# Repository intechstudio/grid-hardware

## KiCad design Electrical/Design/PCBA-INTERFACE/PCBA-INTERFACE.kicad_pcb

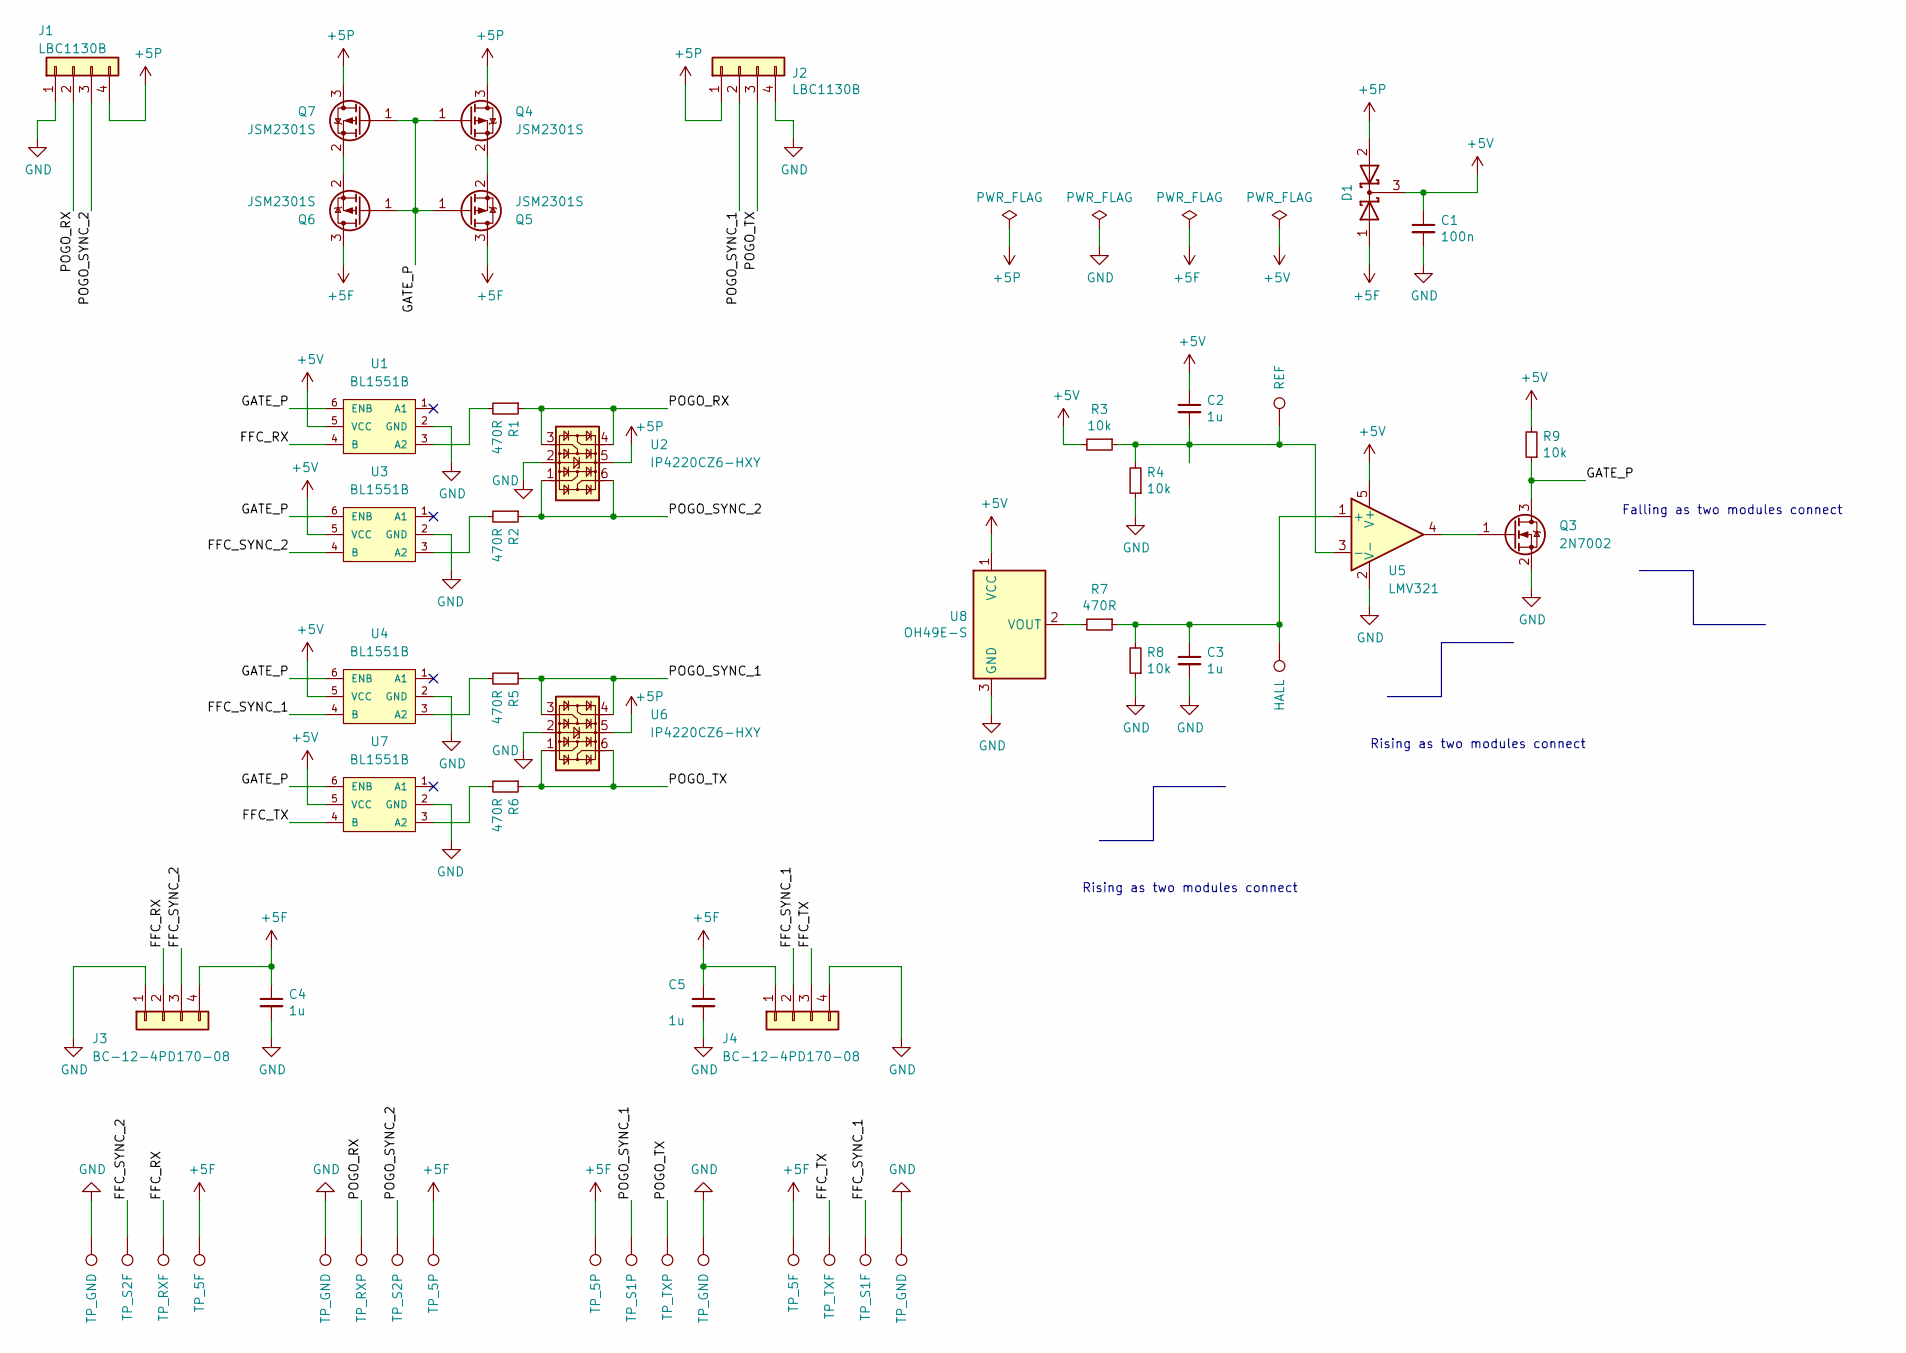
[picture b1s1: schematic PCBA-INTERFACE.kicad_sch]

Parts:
C1: 100n; CAP_0402
C2, C3, C4, C5: 1u; CAP_0402
D1: BAT54C; SOT-23; Part C375703
J1, J2: LBC1130B; J_4xPOGO_SMD; Part LBC1130B
J3, J4: BC-12-4PD170-08; J_BATTERY_CONN
Q3: 2N7002; SOT-23
Q4, Q5, Q6, Q7: JSM2301S; SOT-23
R1, R2, R5, R6, R7: 470R; RES_0402
R3, R4, R8, R9: 10k; RES_0402
TP1: REF; TestPoint_THTPad_1.0x1.0mm_Drill0.5mm
TP2: HALL; TestPoint_THTPad_1.0x1.0mm_Drill0.5mm
TP3, TP7, TP14, TP18: TP_GND; TestPoint_THTPad_1.0x1.0mm_Drill0.5mm
TP4: TP_S2F; TestPoint_THTPad_1.0x1.0mm_Drill0.5mm
TP5: TP_RXF; TestPoint_THTPad_1.0x1.0mm_Drill0.5mm
TP6, TP15: TP_5F; TestPoint_THTPad_1.0x1.0mm_Drill0.5mm
TP8: TP_RXP; TestPoint_THTPad_1.0x1.0mm_Drill0.5mm
TP9: TP_S2P; TestPoint_THTPad_1.0x1.0mm_Drill0.5mm
TP10, TP11: TP_5P; TestPoint_THTPad_1.0x1.0mm_Drill0.5mm
TP12: TP_S1P; TestPoint_THTPad_1.0x1.0mm_Drill0.5mm
TP13: TP_TXP; TestPoint_THTPad_1.0x1.0mm_Drill0.5mm
TP16: TP_TXF; TestPoint_THTPad_1.0x1.0mm_Drill0.5mm
TP17: TP_S1F; TestPoint_THTPad_1.0x1.0mm_Drill0.5mm
U1, U3, U4, U7: BL1551B; SOT-363_SC-70-6
U2, U6: IP4220CZ6-HXY; SOT-23-6-AND-SOT-363; Part C294963
U5: LMV321; SOT-23-5; Part C90297
U8: OH49E-S; SOT-23W; Part C85573

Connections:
+5F: C4.1, C5.1, D1.1 (A), J3.4, J4.1, Q5.3 (D), Q6.3 (D), TP6.1, TP10.1, TP11.1, TP15.1
+5P: D1.2 (A), J1.4, J2.1, Q4.3 (D), Q7.3 (D), U2.5, U6.5
+5V: C1.1, C2.1, D1.3 (K), R3.2, R9.2, U1.5 (VCC), U3.5 (VCC), U4.5 (VCC), U5.5 (V+), U7.5 (VCC), U8.1 (VCC)
/FFC_RX: J3.2, TP5.1, U1.4 (B)
/FFC_SYNC_1: J4.2, TP17.1, U4.4 (B)
/FFC_SYNC_2: J3.3, TP4.1, U3.4 (B)
/FFC_TX: J4.3, TP16.1, U7.4 (B)
/GATE_P: Q3.3 (D), Q4.1 (G), Q5.1 (G), Q6.1 (G), Q7.1 (G), R9.1, U1.6 (ENB), U3.6 (ENB), U4.6 (ENB), U7.6 (ENB)
/POGO_RX: J1.2, R1.1, TP8.1, U2.3, U2.4
/POGO_SYNC_1: J2.2, R5.1, TP12.1, U6.3, U6.4
/POGO_SYNC_2: J1.3, R2.1, TP9.1, U2.1, U2.6
/POGO_TX: J2.3, R6.1, TP13.1, U6.1, U6.6
GND: C1.2, C3.2, C4.2, C5.2, J1.1, J2.4, J3.1, J4.4, Q3.2 (S), R4.1, R8.1, TP3.1, TP7.1, TP14.1, TP18.1, U1.2 (GND), U2.2, U3.2 (GND), U4.2 (GND), U5.2 (V-), U6.2, U7.2 (GND), U8.3 (GND)
unnamed: Q3.1 (G), U5.4
unnamed: Q4.2 (S), Q5.2 (S)
unnamed: Q6.2 (S), Q7.2 (S)
unnamed: R1.2, U1.3 (A2)
unnamed: R2.2, U3.3 (A2)
unnamed: R5.2, U4.3 (A2)
unnamed: C3.1, R7.1, R8.2, TP2.1, U5.1 (+)
unnamed: C2.2, R3.1, R4.2, TP1.1, U5.3 (-)
unnamed: R6.2, U7.3 (A2)
unnamed: R7.2, U8.2 (VOUT)

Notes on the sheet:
Rising as two modules connect
Falling as two modules connect

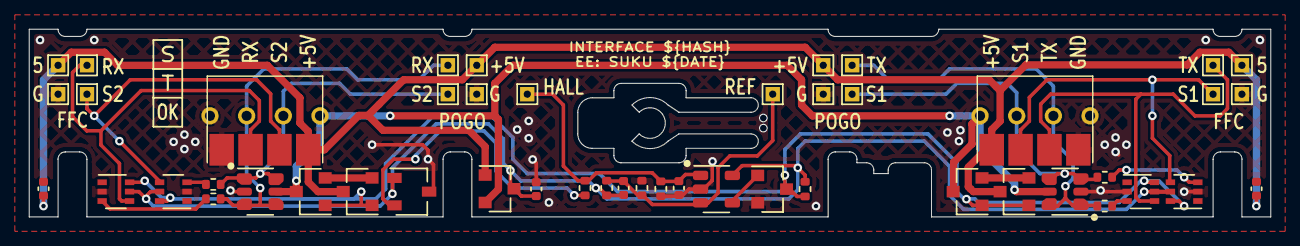
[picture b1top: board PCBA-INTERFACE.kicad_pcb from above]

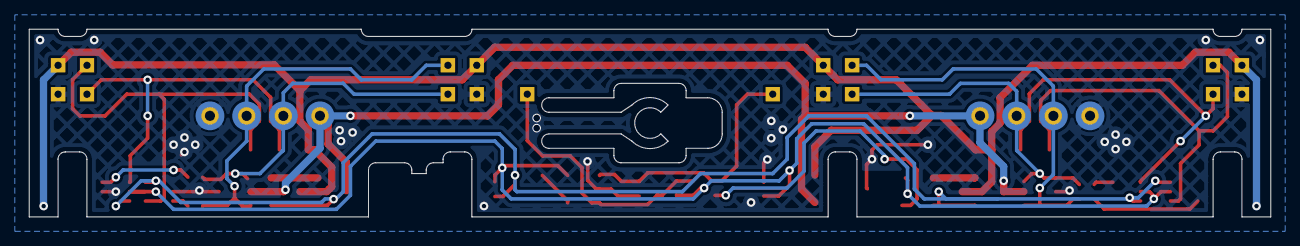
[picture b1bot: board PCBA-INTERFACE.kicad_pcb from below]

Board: 2 copper layers, 86.0 x 13.0 mm, 50 parts (2 on the bottom side), 23 nets.

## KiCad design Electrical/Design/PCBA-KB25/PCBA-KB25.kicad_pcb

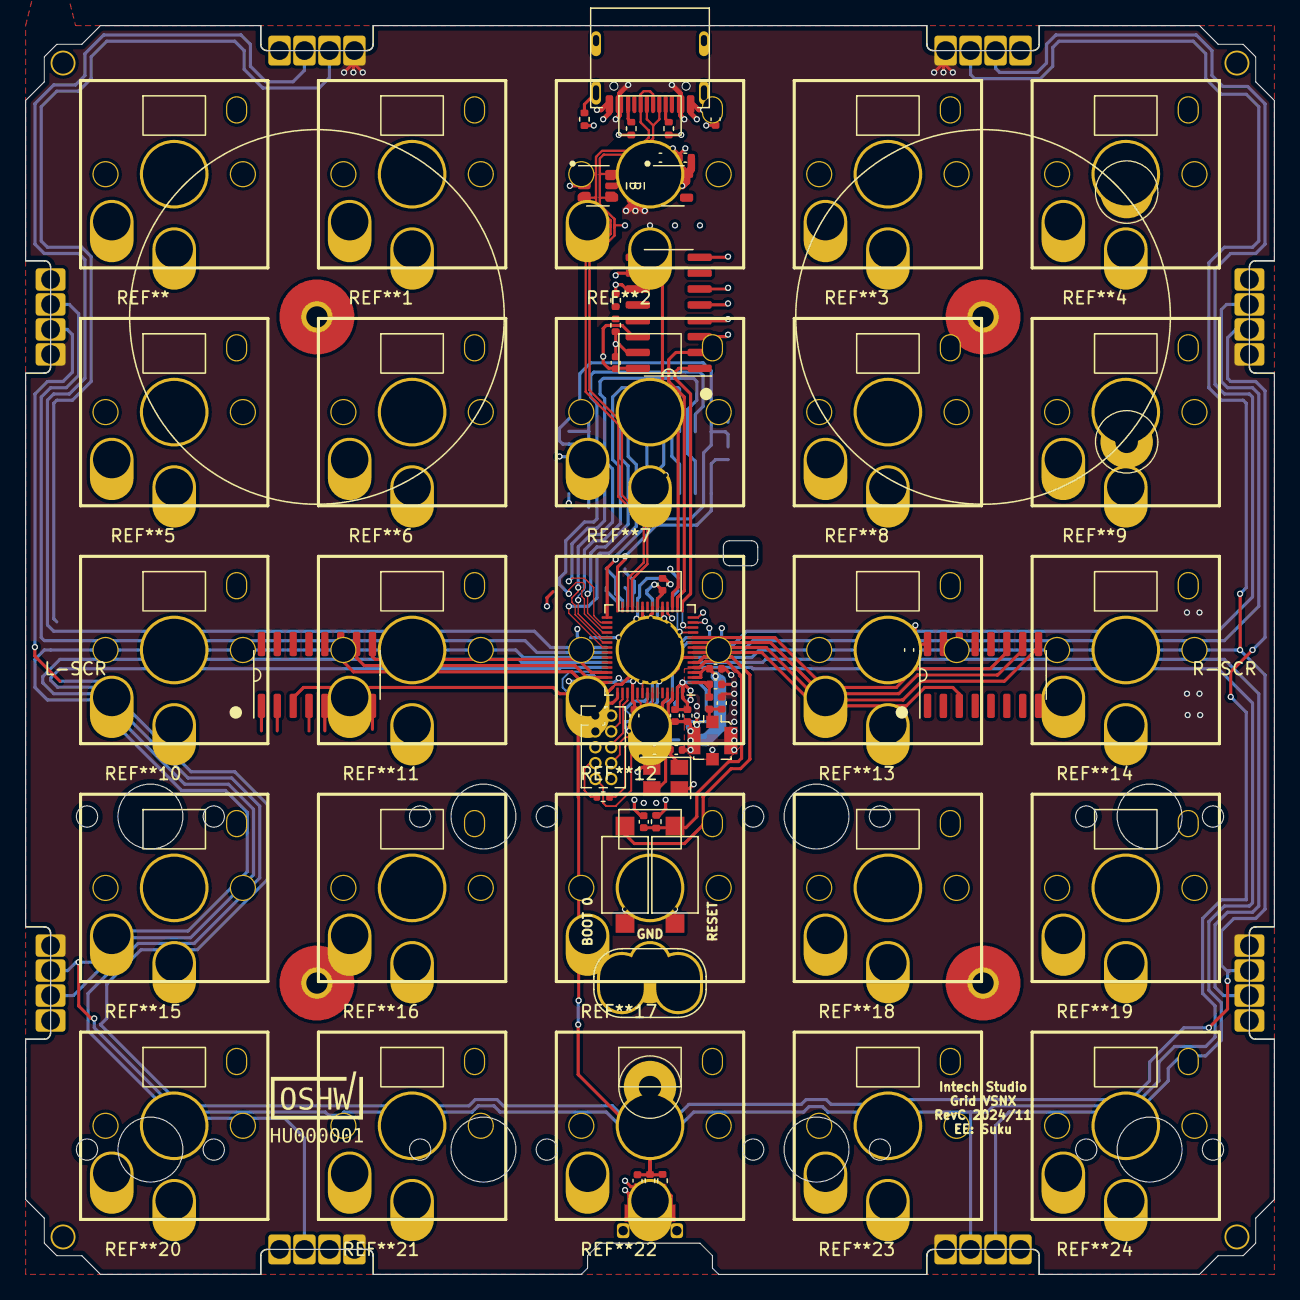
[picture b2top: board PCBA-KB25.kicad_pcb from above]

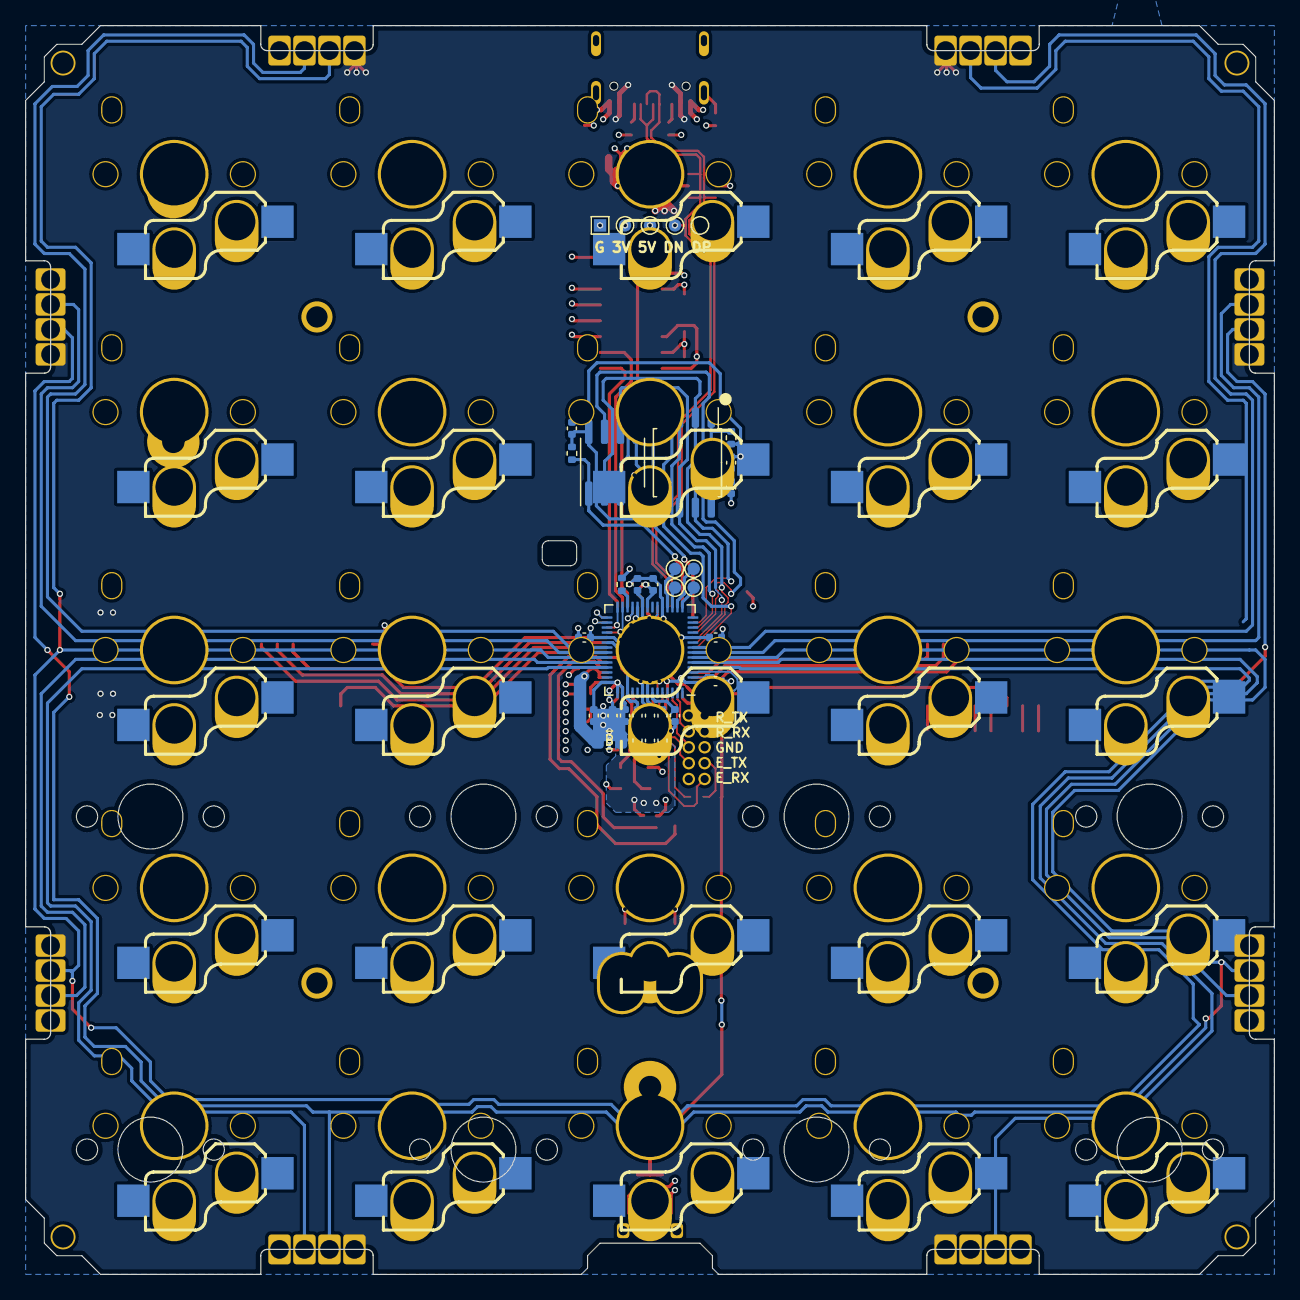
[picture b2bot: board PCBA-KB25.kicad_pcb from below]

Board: 4 copper layers, 100.0 x 100.0 mm, 88 parts (34 on the bottom side), 73 nets.

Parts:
C601, C602, C733, C734, C746, C754, C755, C758: 1u; CAP_0402
C603: 4n7; CAP_0402
C731, C732, C735, C736, C737, C738, C740, C741, C744, C745, C747, C749, C751, C752, C756, C757, C801, C921, C1018: 100n; CAP_0402
C739: 3p9; CAP_0402
C742: 1p8; CAP_0402
C743: 10u; CAP_0402
C748, C750: 10p; CAP_0402
C753: 10n; CAP_0402
H902, H904, H905: MountingHole_Pad; SMD_NUT_M1.6x2.5_FEMALE
J501, J502, J503, J504, J505, J506, J507, J508: Conn_01x04; J_INTERFACE_SPRINGPATTERN
J601: TYPE-C-32-M-12; USB_C_Korean_Hroparts_TYPE-C-31-M-12
J701: C5137195; U.FL_Molex_MCRF_73412-0110_Vertical
J702: Conn_02x05_Odd_Even; PinHeader_2x05_P1.27mm_Vertical
J799: Conn_01x02; OscilloscopeGround
L601, L702: GZ2012D601TF; FERRIT_0805
L701: 1n8; IND_0402
LOGO701: OSHWA
M501: Conn_01x08; grid_outline
R601, R602, R701, R729, R734, R735, R801, R802, R904: 5k1; RES_0402
R603: 1M; RES_0402
R733, R736: 1k; RES_0402
SW701: C255807; SW_HYP_MAPMODE
SW702, SW703: C2905169; SW_SPST_CK_RS282G05A3
TP601: GND; TestPoint_Pad_1.0x1.0mm
TP602: VB; TestPoint_Pad_D1.0mm
TP603: D-; TestPoint_Pad_D1.0mm
TP604: D+; TestPoint_Pad_D1.0mm
TP605: UI; TestPoint_Pad_D1.0mm
TP701, TP702, TP703, TP704: TestPoint; TestPoint_Pad_D1.0mm
U601: C5451661; SOT-23-6-AND-SOT-363
U602: LN1134A332MR-G; SOT-23-5
U703: RP2040; RP2040_QFN-56-1EP_7x7mm_P0.4mm_EP3.2x3.2mm
U704: ESP32-S3FN8; QFN-56-1EP_7x7mm_P0.4mm_EP3.2x3.2mm
U705: W25Q64JVSSIQ; SOIC-8W_FLASH
U801: 74HC165; SOIC-16_74HC165
U903: ESP-PSRAM32; SOIC-8_3.9x4.9mm_P1.27mm
U1001, U1002: 74HC4051; SOIC-16_74HC4051
Y701: 40MHz; Crystal_SMD_Abracon_ABM8G-4Pin_3.2x2.5mm

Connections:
+1V1: C731.1, C732.1, C733.1, U703.23 (DVDD), U703.45 (VREG_VOUT), U703.50 (DVDD)
+3V3: C602.2, C734.1, C735.1, C736.1, C737.1, C738.1, C740.1, C741.1, C743.1, C744.1, C745.1, C746.1, C747.1, C751.1, C752.1, C753.1, C754.1, C757.2, C801.1, C1018.1, L702.2, R701.1, R729.1, R735.1, TP605.1, U602.5 (OUT), U703.1 (IOVDD), U703.10 (IOVDD), U703.22 (IOVDD), U703.33 (IOVDD), U703.42 (IOVDD), U703.43 (ADC_AVDD), U703.44 (VREG_IN), U703.48 (USB_VDD), U703.49 (IOVDD), U704.20 (VDD3P3_RTC), U704.46 (VDD3P3_CPU), U704.55 (VDDA1), U704.56 (VDDA2), U801.3 (D4), U801.6 (D7), U801.14 (D3), U801.16 (VCC), U1001.16 (VDD), U1002.16 (VDD)
+5V: J501.1, J502.4, J503.1, J504.4, J505.4, J506.1, J507.4, J508.1, J601.A4B9 (VBUS), J601.A9B4 (VBUS), L601.2, TP602.1, U601.5
/HWCFG/HWCFG_CLOCK: U704.16 (GPIO11), U801.2 (CLK)
/HWCFG/HWCFG_DATA: U704.17 (GPIO12), U801.9 (Q)
/HWCFG/HWCFG_SHIFT: U704.15 (GPIO10), U801.1 (SH/~LD)
/MCU/ESP_BOOT0: SW703.2 (B), U704.5 (GPIO0)
/MCU/ESP_LNA: C742.1, L701.2, U704.1 (LNA_IN)
/MCU/ESP_RESET: C758.1, R735.2, SW702.2 (B), U704.4 (CHIP_PU)
/MCU/GRID_EAST_RX: J503.3, U703.36 (GPIO24)
/MCU/GRID_EAST_TX: J505.2, U703.38 (GPIO26_ADC0)
/MCU/GRID_NORTH_RX: J501.3, U703.8 (GPIO6)
/MCU/GRID_NORTH_TX: J502.2, U703.35 (GPIO23)
/MCU/GRID_SOUTH_RX: J508.3, U703.39 (GPIO27_ADC1)
/MCU/GRID_SOUTH_TX: J507.2, U703.4 (GPIO2)
/MCU/GRID_SYNC_1: J502.3, J504.3, J505.3, J507.3, U703.37 (GPIO25)
/MCU/GRID_SYNC_2: J501.2, J503.2, J506.2, J508.2, U703.6 (GPIO4)
/MCU/GRID_WEST_RX: J506.3, U703.5 (GPIO3)
/MCU/GRID_WEST_TX: J504.2, U703.7 (GPIO5)
/MCU/MAP_MODE: C757.1, R701.2, R736.2, U704.43 (GPIO38)
/MCU/RP_CLK: U703.20 (XIN), U704.21 (GPIO15)
/MCU/RP_INTERRUPT: U703.34 (GPIO22), U704.23 (GPIO17)
/MCU/RP_RUN: R729.2, U703.26 (RUN)
/MCU/RP_SPI0_CS: U703.28 (GPIO17), U704.12 (GPIO7)
/MCU/RP_SPI0_RX: U703.27 (GPIO16), U704.11 (GPIO6)
/MCU/RP_SPI0_SCK: U703.29 (GPIO18), U704.14 (GPIO9)
/MCU/RP_SPI0_TX: U703.30 (GPIO19), U704.13 (GPIO8)
/MCU/RP_SWCLK: U703.24 (SWCLK), U704.19 (GPIO14)
/MCU/RP_SWDIO: U703.25 (SWD), U704.18 (GPIO13)
/MCU/RP_UART0_RX: J702.3, U703.3 (GPIO1)
/MCU/RP_UART0_TX: J702.1, U703.2 (GPIO0)
/MCU/SPICLK: U704.33 (GPIO30), U705.6 (CLK), U903.6 (SCLK)
/MCU/SPICS0: R734.2, U704.32 (GPIO29), U705.1 (~CS)
/MCU/SPICS1: R904.2, U704.28 (GPIO26), U903.1 (~CE)
/MCU/SPID: U704.35 (GPIO32), U705.5 (DI(IO0)), U903.5 (SI/SIO)
/MCU/SPIHD: U704.30 (GPIO27), U705.7 (IO3), U903.7 (SIO3)
/MCU/SPIQ: U704.34 (GPIO31), U705.2 (DO(IO1)), U903.2 (SO/SIO)
/MCU/SPIWP: U704.31 (GPIO28), U705.3 (IO2), U903.3 (SIO2)
/MCU/TCK: J702.4, U704.44 (GPIO39)
/MCU/TDI: J702.8, U704.47 (GPIO41)
/MCU/TDO: J702.6, U704.45 (GPIO40)
/MCU/TMS: J702.2, U704.48 (GPIO42)
/MCU/U0RXD: J702.9, U704.50 (GPIO44)
/MCU/U0TXD: R733.2, U704.49 (GPIO43)
/MCU/USB_DN: J601.A7 (D-), J601.B7 (D-), TP603.1, U601.4, U601.6, U704.25 (GPIO19)
/MCU/USB_DP: J601.A6 (D+), J601.B6 (D+), TP604.1, U601.1, U601.3, U704.26 (GPIO20)
ESP_GPIO_1: U704.6 (GPIO1), U1001.3 (X)
ESP_GPIO_2: U704.7 (GPIO2), U1002.3 (X)
ESP_GPIO_3: U704.8 (GPIO3), U1002.9 (C)
ESP_GPIO_4: U704.9 (GPIO4), U1002.10 (B)
ESP_GPIO_5: U704.10 (GPIO5), U1002.11 (A)
ESP_GPIO_35: U704.40 (GPIO35), U1001.9 (C)
ESP_GPIO_36: U704.41 (GPIO36), U1001.10 (B)
ESP_GPIO_37: U704.42 (GPIO37), U1001.11 (A)
GND: C601.2, C602.1, C603.2, C731.2, C732.2, C733.2, C734.2, C735.2, C736.2, C737.2, C738.2, C739.2, C740.2, C741.2, C742.2, C743.2, C744.2, C745.2, C746.2, C747.2, C748.2, C749.2, C750.2, C751.2, C752.2, C753.2, C754.2, C755.2, C756.2, C758.2, C801.2, C921.2, C1018.2, H902.1, H904.1, H905.1, J501.4, J502.1, J503.4, J504.1, J505.1, J506.4, J507.1, J508.4, J601.A1B12 (GND), J601.A12B1 (GND), J701.2 (Ext), J702.5, J799.1, J799.2, R601.2, R602.2, R603.2, R801.2, R802.2, SW701.2 (B), SW702.1 (A), SW703.1 (A), TP601.1, U601.2, U602.2 (GND), U703.19 (TESTEN), U703.57 (GND), U704.57 (GND), U705.4 (GND), U801.4 (D5), U801.5 (D6), U801.8 (GND), U801.10 (SI), U801.11 (D0), U801.15 (INH), U903.4 (VSS), U1001.6 (Inh), U1001.7 (VEE), U1001.8 (VSS), U1002.6 (Inh), U1002.7 (VEE), U1002.8 (VSS), Y701.2, Y701.4
unnamed: C603.1, J601.S1 (SHIELD)
unnamed: C749.1, L702.1, U704.2 (VDD3P3), U704.3 (VDD3P3)
unnamed: J601.A5 (CC1), R601.1
unnamed: J601.B5 (CC2), R602.1
unnamed: J601.S2 (SHIELD), R603.1
unnamed: C739.1, J701.1 (In), L701.1
unnamed: J702.7, R733.1
unnamed: R801.1, U801.12 (D1)
unnamed: R802.1, U801.13 (D2)
unnamed: R736.1, SW701.1 (A)
unnamed: C601.1, L601.1, U602.1 (IN), U602.3 (EN)
unnamed: TP701.1, U703.15 (GPIO12)
unnamed: TP702.1, U703.16 (GPIO13)
unnamed: TP703.1, U703.17 (GPIO14)
unnamed: TP704.1, U703.18 (GPIO15)
unnamed: C750.1, U704.53 (XTAL_N), Y701.3
unnamed: C748.1, U704.54 (XTAL_P), Y701.1
VDD_SPI: C755.1, C756.1, C921.1, R734.1, R904.1, U704.29 (VDD_SPI), U705.8 (VCC), U903.8 (VCC)
